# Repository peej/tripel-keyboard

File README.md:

# Tripel - Ortholinear 60% keyboard PCB

Tripel is a 15 column ortholinear keyboard PCB.

The goal of this project is to build an all throughhole component, pro-micro powered ortholinear PCB that fits in a standard 60% tray mount case but built from sub-100x100mm PCB boards.

Inspired by the modular PCB projects of [40Percent.club](http://www.40percent.club/) like the [Nori](http://www.40percent.club/2018/10/nori.html).

* Designed to be easy to build with minimal soldering experience.
* Built from 3 of the same PCB.
* 7u spacebar bottom row.

# Bill of Materials (BOM)

* 3 PCBs.
* A suitable 60% ortholinear keyboard plate (eg. [XD75 plate](https://kprepublic.com/collections/xd75/products/stainless-steel-plate-for-xd75re-60-custom-keyboard-mechanical-keyboard-plate-support-xd75re)).
* 65 MX compatible switches.
* 65 1n4148 diodes.
* Pro Micro controller (or compatible alternative).
* 7u PCB mount stabilizer.
* Through-hole USB mini or micro connector.
* USB cable for Pro Micro.

# Ordering PCBs

PCBs can be manufactuered by a variety of online PCB fabricators. You can use [PCBShopper](https://pcbshopper.com/) to search for the best price. Many manufacturers have special rates for prototype boards under 100x100mm in size.

The zip file in the gerber directory contains the gerber files your fabricator will need to make the PCB [tripel.zip](https://github.com/peej/tripel-keyboard/blob/master/gerber/tripel.zip) PCB.

When uploading the gerber zip files, use the default PCB settings.

# Construction

* You will need 3 PCBs.
* Solder the diodes onto each PCB.
  * You can place them on either side, but the drawing on the soldermask is on the front of the PCB.
  * The diodes under the Pro Micro must go on the front side of the PCB.
  * The end of the diode with black band goes in the square hole.
* Solder on the Pro Micro headers onto the underside of one PCB.
  * Do not solder on the Pro Micro yet.
  * You can place the Pro Micro on any of the 3 PCBs, pick the placement that works best for your case.
  * To get keep the headers straight while soldering, place the Pro Micro over the headers to hold them in place.
  * If you want to use a socket for your Pro Micro, solder on a socket instead.
* Solder on the USB connector to the underside of the left PCB.
* Insert the switches into the plate.
  * If using a XD75 ortholinear plate, you will need to modify it if you are using an incompatible layout.
* Join the PCBs together by solder the solder bridges between the PCBs.
  * Solder all pad bridges between the 3 PCBs.
  * Use small bent pieces of trimmed diode wire to bridge the solder bridges instead of just using solder.
* Put the 7u stabilizer together and fit it into the left and right PCBs.
  * If you are using the standard modifier keycap sizes, you will also want to add 2u stabs for those keys.
  * If you forget the stabilizer you will need to unsolder all of the switches so as to fit it.
  * Don't forget to trim and lube your stabilizer before fitting if you want to.
* Place the PCBs onto the switches:
  * Insert all the switches and ensure that the pins of each switch are correctly coming through the board and are not bent under the PCB.
* Solder all the switch pins.
  * Some switches might foul on your case mounting posts stopping the PCB from sitting flush, before soldering, trim the switch pins which would foul so they are flush with the PCB.
  * The switch next to the Pro Micro might need to have it's pins trimmed so that your USB cable can plug in and sit as flush as possible to the PCB.
* Solder on the Pro Micro:
  * Ensure that you have it the correct way around, the chip side should be face down towards the PCB with the USB port to the right.
  * You might want to plug in your USB cable while soldering so that the Pro Micro is mounted far enough from the PCB for the cable to plug in successfully.
  * Use electrical tape underneath the Pro Micro if you think shorting against the switch pins could be an issue.
* Cut your USB cable to length and solder the wires to the pads for the USB connector.
 * Wire colours may vary, but usually: Red = VCC; black = GND; white = D-; green = D+

# Firmware

Build and flash the Pro Micro with QMK firmware, see the [QMK documentation](http://qmk.fm/) on how to do this.

The required pinout for the firmware is shown in [this KLE layout](http://www.keyboard-layout-editor.com/#/gists/6fe5d6cc536d3c9c028186f25ce0c42f):

A preconfigured firmware is not yet available in the QMK repo but can be [found here in my fork](https://github.com/peej/qmk_firmware/tree/master/keyboards/tripel).

# Differences to the XD75

The main difference to the XD75 is the alternative layout options.

* Supports PCB mount stabilizers for a 7u (or 2u) "spacebar"
* Supports PCB mount stabilizers for non-1u layout, 2u "backspace", 2.75u "enter" and "right shift" keys.
* The Tripel does not support the full-grid layout of the XD75 as there are not enough pins on the Pro Micro

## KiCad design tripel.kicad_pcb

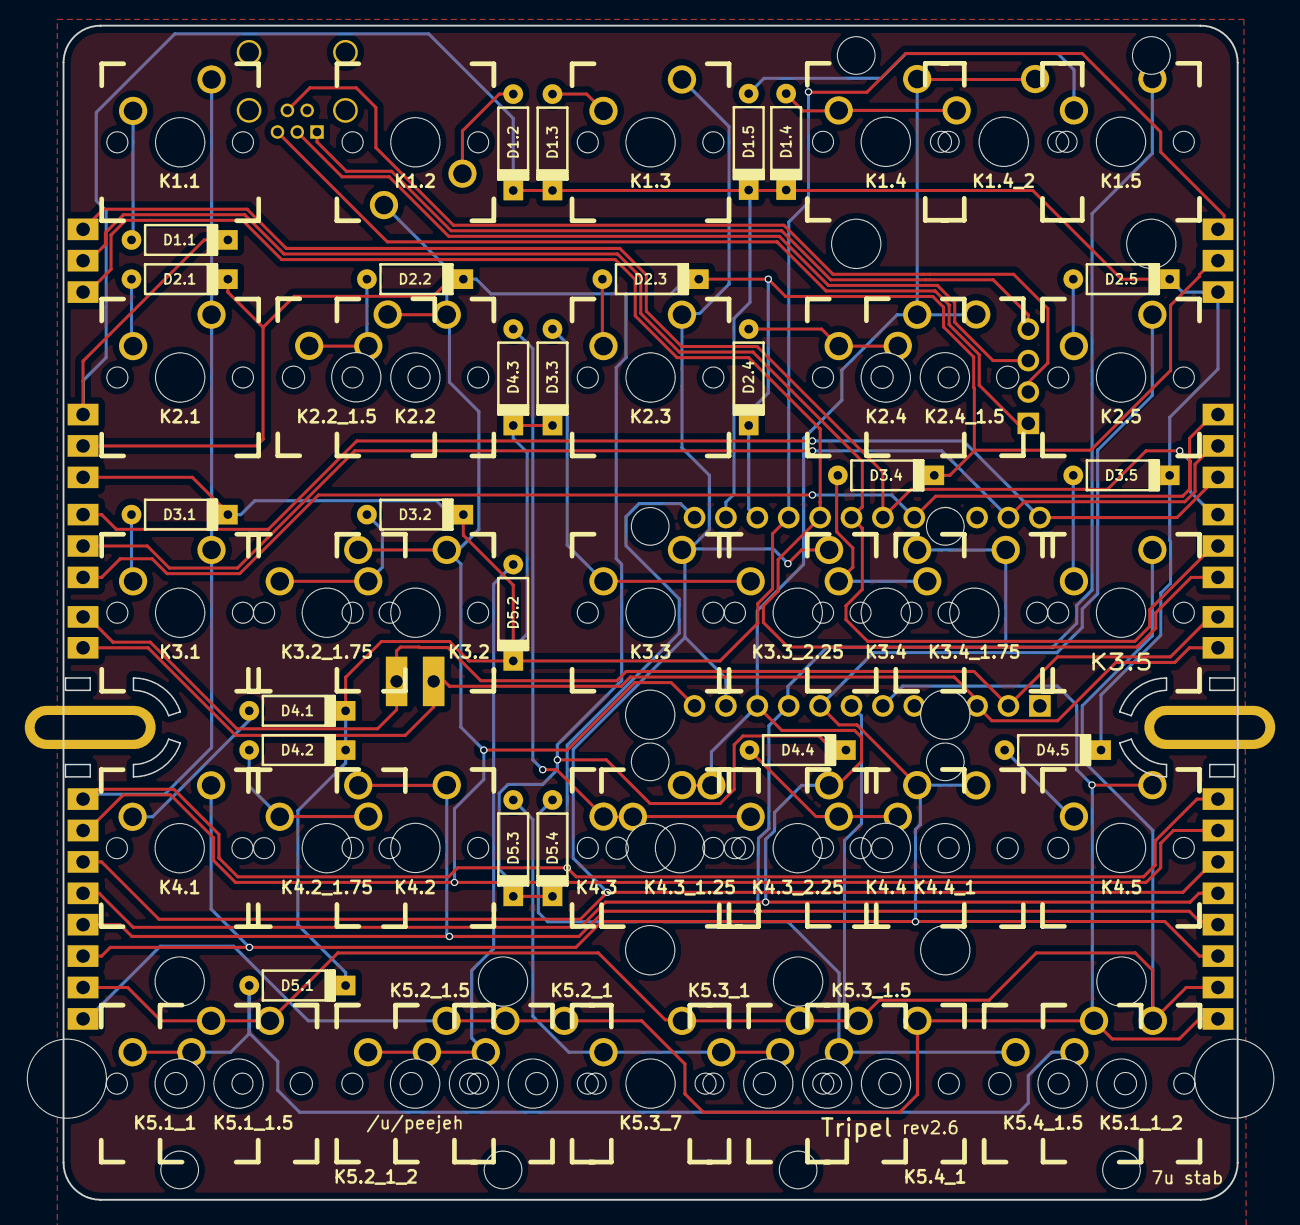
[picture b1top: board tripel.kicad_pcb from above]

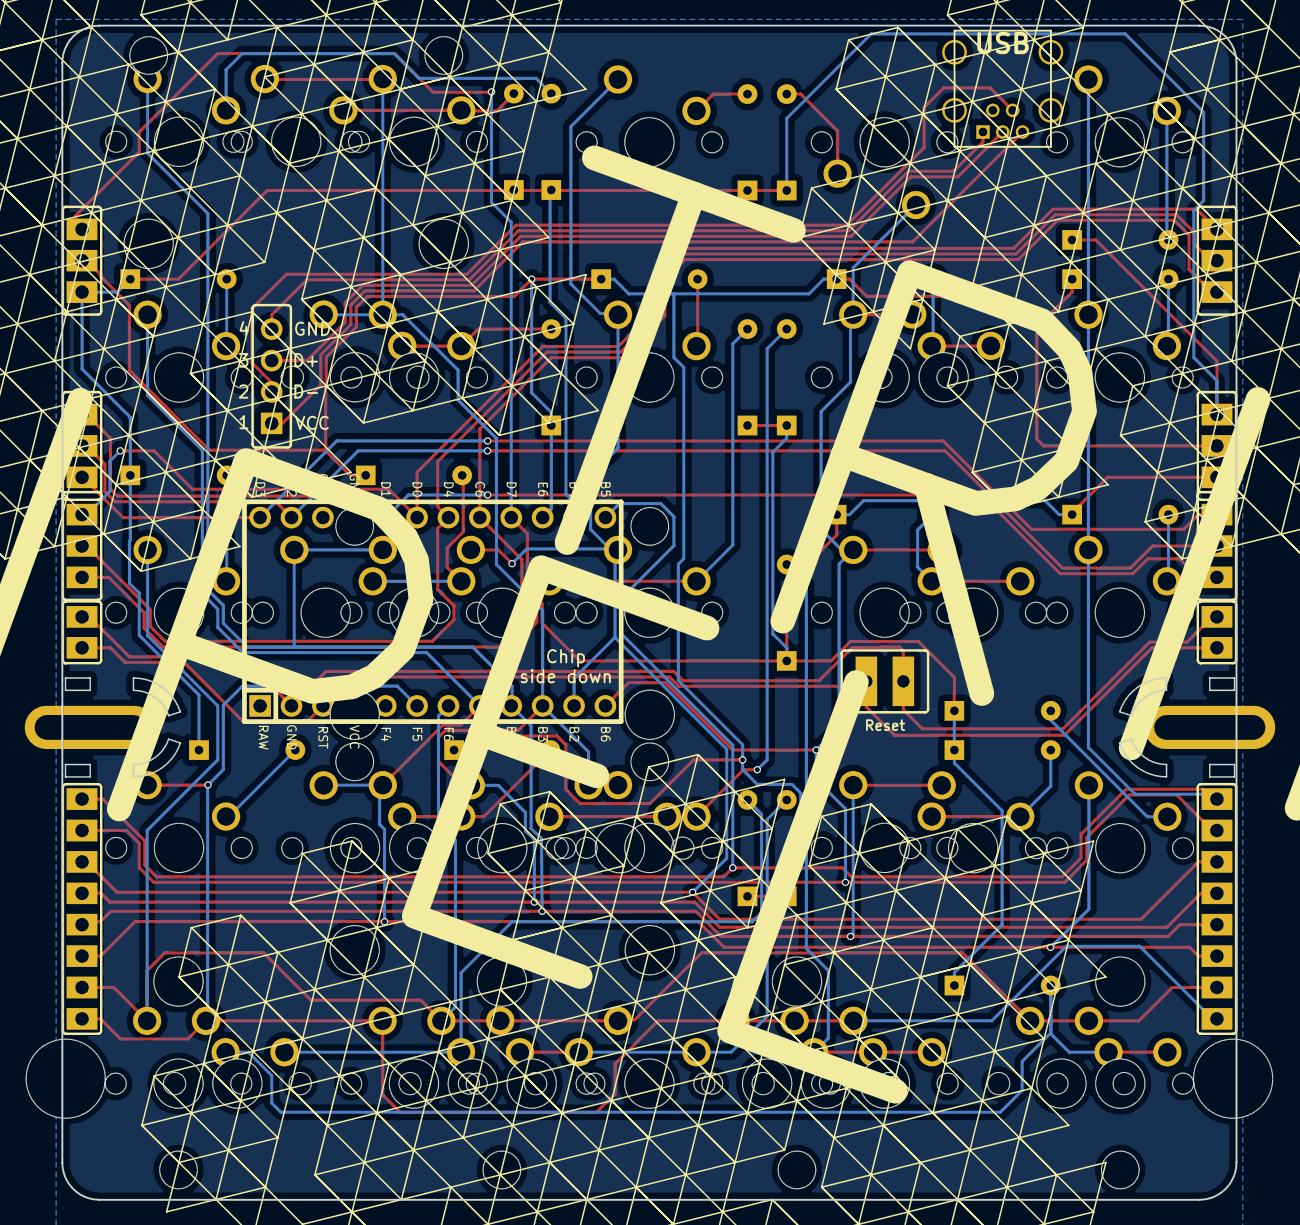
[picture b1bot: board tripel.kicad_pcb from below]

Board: 2 copper layers, 95.0 x 95.0 mm, 79 parts (14 on the bottom side), 47 nets.

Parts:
D1.1, D1.2, D1.3, D1.4, D1.5, D2.1, D2.2, D2.3, D2.4, D2.5, D3.1, D3.2, D3.3, D3.4, D3.5, D4.1, D4.2, D4.3, D4.4, D4.5, D5.1, D5.2, D5.3, D5.4: D; DIODE
J1: Left Columns; CONNECTOR_8
J2, J5: Left Rows; CONNECTOR_3
J3, J8: Right Rows; CONNECTOR_3
J4: Right Columns; CONNECTOR_8
J6: USB_mini_micro_B; USB_Mini-B
J7: Conn_01x04; CONNECTOR_4
J9: Reset; RESET
J10: Right Reset; CONNECTOR_2
J11: Left Reset; CONNECTOR_2
J12, J13: Far Left Rows; CONNECTOR_3
K1.1, K1.2, K1.3, K1.4, K1.5, K2.1, K2.2, K2.3, K2.4, K2.5, K3.1, K3.2, K3.3, K3.4, K3.5, K4.1, K4.2, K4.3, K4.4, K4.4_1, K4.5, K5.1_1, K5.1_1_2, K5.2_1, K5.2_1_2, K5.3_1, K5.4_1: KEYSW; MX
K1.4_2, K5.3_7: KEYSW; MX_PCB_200H
K2.2_1.5, K2.4_1.5, K5.1_1.5, K5.2_1.5, K5.3_1.5, K5.4_1.5: KEYSW; MX_PCB_150H
K3.2_1.75, K3.4_1.75, K4.2_1.75: KEYSW; MX_PCB_175H
K3.3_2.25, K4.3_2.25: KEYSW; MX_PCB_225H
K4.3_1.25: KEYSW; MX_PCB_125H
U1: ProMicro_ChipSideDown; Pro_Micro_ChipSideDown

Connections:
unnamed: D1.1.1, D1.2.1, D1.3.1, D1.4.1, D1.5.1, D2.5.1, D3.5.1, D4.5.1, J5.1, J8.3, U1.23
unnamed: D1.1.2, K1.1.2
unnamed: D1.2.2, K1.2.2
unnamed: D1.3.2, K1.3.2
unnamed: D1.4.2, K1.4.2, K1.4_2.2
unnamed: D1.5.2, K1.5.2
unnamed: D2.1.1, D2.2.1, D2.3.1, D2.4.1, D3.4.1, D4.4.1, D5.3.1, D5.4.1, J5.2, J8.2, U1.22
unnamed: D2.1.2, K2.1.2
unnamed: D2.2.2, K2.2.2, K2.2_1.5.2
unnamed: D2.3.2, K2.3.2
unnamed: D2.4.2, K2.4.2, K2.4_1.5.2
unnamed: D2.5.2, K2.5.2
unnamed: D3.1.1, D3.2.1, D3.3.1, D4.1.1, D4.2.1, D4.3.1, D5.1.1, D5.2.1, J5.3, J8.1, U1.21
unnamed: D3.1.2, K3.1.2
unnamed: D3.2.2, K3.2.2, K3.2_1.75.2
unnamed: D3.3.2, K3.3.2, K3.3_2.25.2
unnamed: D3.4.2, K3.4.2, K3.4_1.75.2
unnamed: D3.5.2, K3.5.2
unnamed: D4.1.2, K4.1.2
unnamed: D4.2.2, K4.2.2, K4.2_1.75.2
unnamed: D4.3.2, K4.3.2, K4.3_1.25.2, K4.3_2.25.2
unnamed: D4.4.2, K4.4.2, K4.4_1.2
unnamed: D4.5.2, K4.5.2
unnamed: D5.1.2, K5.1_1.2, K5.1_1.5.2, K5.1_1_2.2
unnamed: D5.2.2, K5.2_1.2, K5.2_1.5.2, K5.2_1_2.2
unnamed: D5.3.2, K5.3_1.2, K5.3_1.5.2, K5.3_7.2
unnamed: D5.4.2, K5.4_1.2, K5.4_1.5.2
unnamed: J1.1, J4.1, K4.5.1, K5.2_1.1, K5.2_1.5.1, K5.2_1_2.1, K5.4_1.1, K5.4_1.5.1, U1.6
unnamed: J1.2, J4.2, K3.5.1, K5.1_1.1, K5.1_1.5.1, K5.1_1_2.1, K5.3_1.1, K5.3_1.5.1, K5.3_7.1, U1.7
unnamed: J1.3, J4.3, K2.5.1, K4.1.1, K4.4.1, K4.4_1.1, U1.8
unnamed: J1.4, J4.4, K1.5.1, K3.4.1, K3.4_1.75.1, K4.2.1, K4.2_1.75.1, U1.9
unnamed: J1.5, J4.5, K1.4.1, K1.4_2.1, K2.4.1, K2.4_1.5.1, K4.3.1, K4.3_1.25.1, K4.3_2.25.1, U1.10
unnamed: J1.6, J4.6, K1.3.1, K2.3.1, K3.3.1, K3.3_2.25.1, U1.11
unnamed: J1.7, J4.7, K1.2.1, K2.2.1, K2.2_1.5.1, K3.2.1, K3.2_1.75.1, U1.12
unnamed: J1.8, J4.8, K1.1.1, K2.1.1, K3.1.1, U1.24
unnamed: J6.1, J7.1
unnamed: J6.2, J7.2
unnamed: J6.3, J7.3
unnamed: J6.5, J7.4
unnamed: J9.1, J10.1, J11.1, U1.2
unnamed: J9.2, J10.2, J11.2, U1.3
unnamed: J3.1, J12.1, U1.20
unnamed: J3.2, J12.2, U1.19
unnamed: J3.3, J12.3, U1.18
unnamed: J2.1, J13.1, U1.17
unnamed: J2.2, J13.2, U1.14
unnamed: J2.3, J13.3, U1.13

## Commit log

2019-10-01 Add prototype PCB image
2019-10-01 Update instructions
2019-10-10 Add split spacebar bottom row
2019-10-25 Update construction documentation
2019-10-25 Increase size of mounting hole to ease case installation
2019-10-29 Flip stabilizer mounting holes
2019-10-29 Update construction instructions
2019-11-01 Fix right side PCB connection
2019-11-02 Adjust connector pad positions
2019-11-02 Switch to single sided design
2019-11-02 Update documentation
2019-11-03 Add some backside silkscreen patterns
2019-11-16 Add 4x1u bottom row option
2019-11-16 Fix Pro Micro silkmask
2019-11-16 Breakout reset pads
2019-11-18 Update gerbers zip
2019-11-18 Update PCB images
2019-11-23 Rename diodes to match the name of their corrisponding switch
2019-11-24 Add images directory and add layout image
2019-12-10 Move USB pads to more convenient location
2019-12-14 Flip USB footprint to correct side of board
2019-12-28 Add switch footprints for alternative mod sizes
    This introduces a number of changes so as toallow standard sized mod keys to be used. This required moving of a number of components so as to make space for 2u key stabilizers.
    Changes include:
    * Move Pro-Micro to the right to avoid stabilizer mounting holes
    * Add extra connections between boards to allow Pro-Micro to be placed on any of the PCBs
    * Remove USB pertrusion and flip orientation of K1.2 to be north facing
    * Add extra connections so that reset pads can be accessed via hole in case even in Pro-Micro is on a different PCB
2019-12-28 Update PCB render
2020-01-03 Add split right shift and 1.75u enter options
2020-02-02 Add stab holes for 2u backspace
2020-02-16 Update README and add additional images
2020-09-13 Move inter-PCB contacts away from PCB edge to help prevent shorts
2020-09-16 Add removable mounting holes
2020-09-18 Change USB header pin spacing to standard size
